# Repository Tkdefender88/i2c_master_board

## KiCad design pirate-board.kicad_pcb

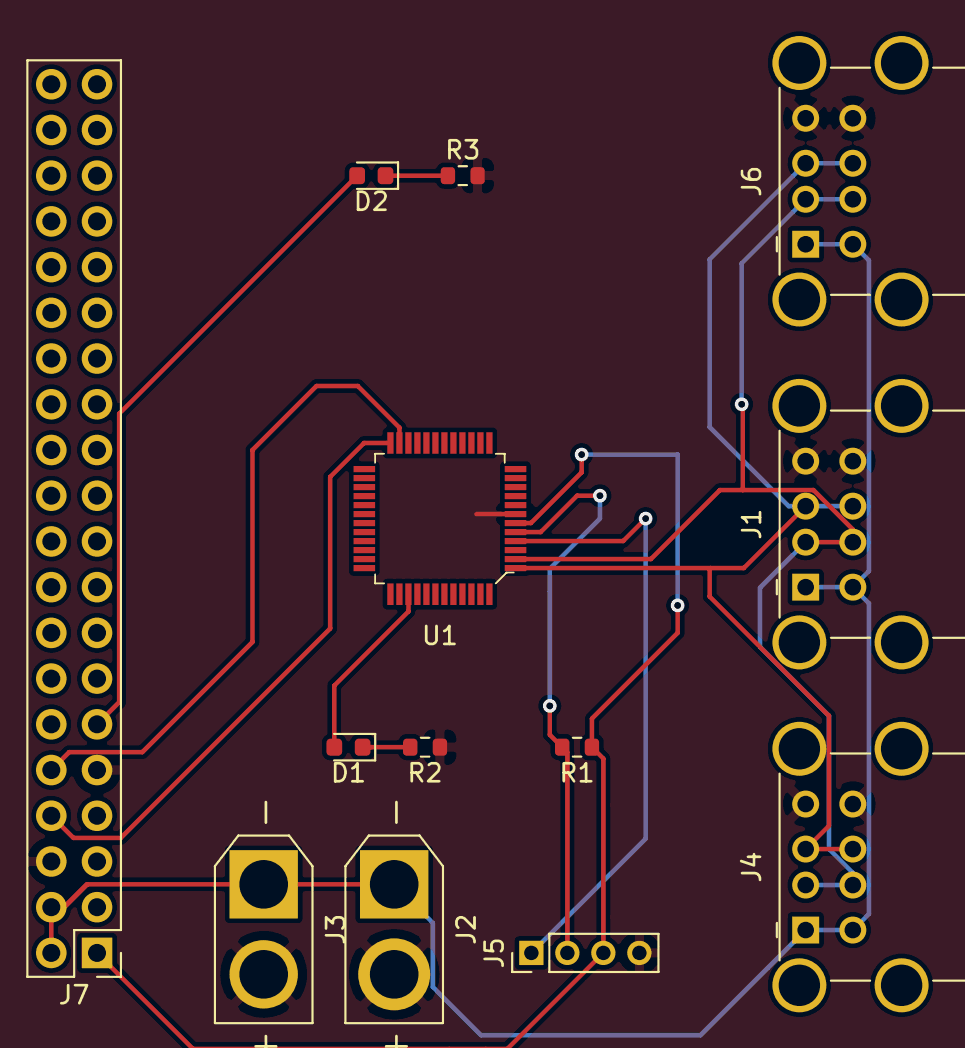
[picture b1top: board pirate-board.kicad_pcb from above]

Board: 2 copper layers, 13 parts (0 on the bottom side), 13 nets.

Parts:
D1, D2: LED; D_0603_1608Metric
J1, J4, J6: USB_A_Stacked; USB_A_Wuerth_61400826021_Horizontal_Stacked
J2: xt_30; AMASS_XT30U-F_1x02_P5.0mm_Vertical
J3: xt_30; AMASS_XT30U-M_1x02_P5.0mm_Vertical
J5: Conn_01x04_Male; PinHeader_1x04_P2.00mm_Vertical
J7: Raspberry_Pi_2_3; PinHeader_2x20_P2.54mm_Vertical
R1, R2, R3: 1k; R_0603_1608Metric
U1: MSP430FR2355; LQFP-48_7x7mm

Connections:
GND: J1.4, J1.8, J2.2, J3.2, J4.4, J4.8, J5.4, J6.4, J6.8, J7.6, J7.9, R2.1, R3.2, U1.7
unnamed: D1.1, R2.2
unnamed: D1.2, U1.39
unnamed: D2.1, R3.1
unnamed: D2.2, J7.11
unnamed: J1.2, J1.6, J4.2, J4.6, J6.2, J6.6, U1.2
unnamed: J1.3, J1.7, J4.3, J4.7, J6.3, J6.7, U1.1
unnamed: J5.1, U1.4
unnamed: J5.2, R1.2, U1.5
unnamed: J5.3, J7.1, R1.1, U1.6
unnamed: J7.8, U1.24
unnamed: J7.10, U1.23
VCC: J1.1, J1.5, J2.1, J3.1, J4.1, J4.5, J6.1, J6.5, J7.2, J7.4

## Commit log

2021-11-12 init
2021-11-12 generated gerbers
2021-11-12 modified board layout
